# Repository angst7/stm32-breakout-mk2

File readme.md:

#STM32F4 development board#

ARMKit2 Breakout and development board for the 64-pin LQFP STM32F405 microcontroller.

The STM32F405 is a 32-bit ARM Cortex M4 micro manufactured by ST Microelectronics.

This PCB breaks out all the GPIO pins in two 2x16 pin 0.1" headers.  Power is provided by a USB mini-B connector through a 3.3v LDO regulator.  The USB data pins are routed to the port A USB peripheral in order to enable use of ST's built-in bootloader.  A Boot-select button is provided to enable this. 

The design is intended to be as bare-bones as possible, while enabling access to most of the important chip features.  Other features of this design are:

* Reset button.
* Two LEDs on-board.
* Optional External HS Oscillator
* Optional External RTC Oscillator
* Standard 6-Pin programming header for ST/Link
* 3mm mounting holes

Available as a shared project on [OSHPark](https://oshpark.com/profiles/MonkeyKungFu)

##Note regarding part population##

For STM32F405 parts, Populate C1 and C3 with 2.2uF capacitors.  Do not populate C5, R9.
For STM32F41x, STM32F4x1 parts, Populate R9 and C1 with 0 ohm Resistor.  Populate C5 with 4.7uF capacitor.  Do not populate C3.

##License##

This work is licensed under [CC Attribution 3.0 United States](https://creativecommons.org/licenses/by/3.0/us/).

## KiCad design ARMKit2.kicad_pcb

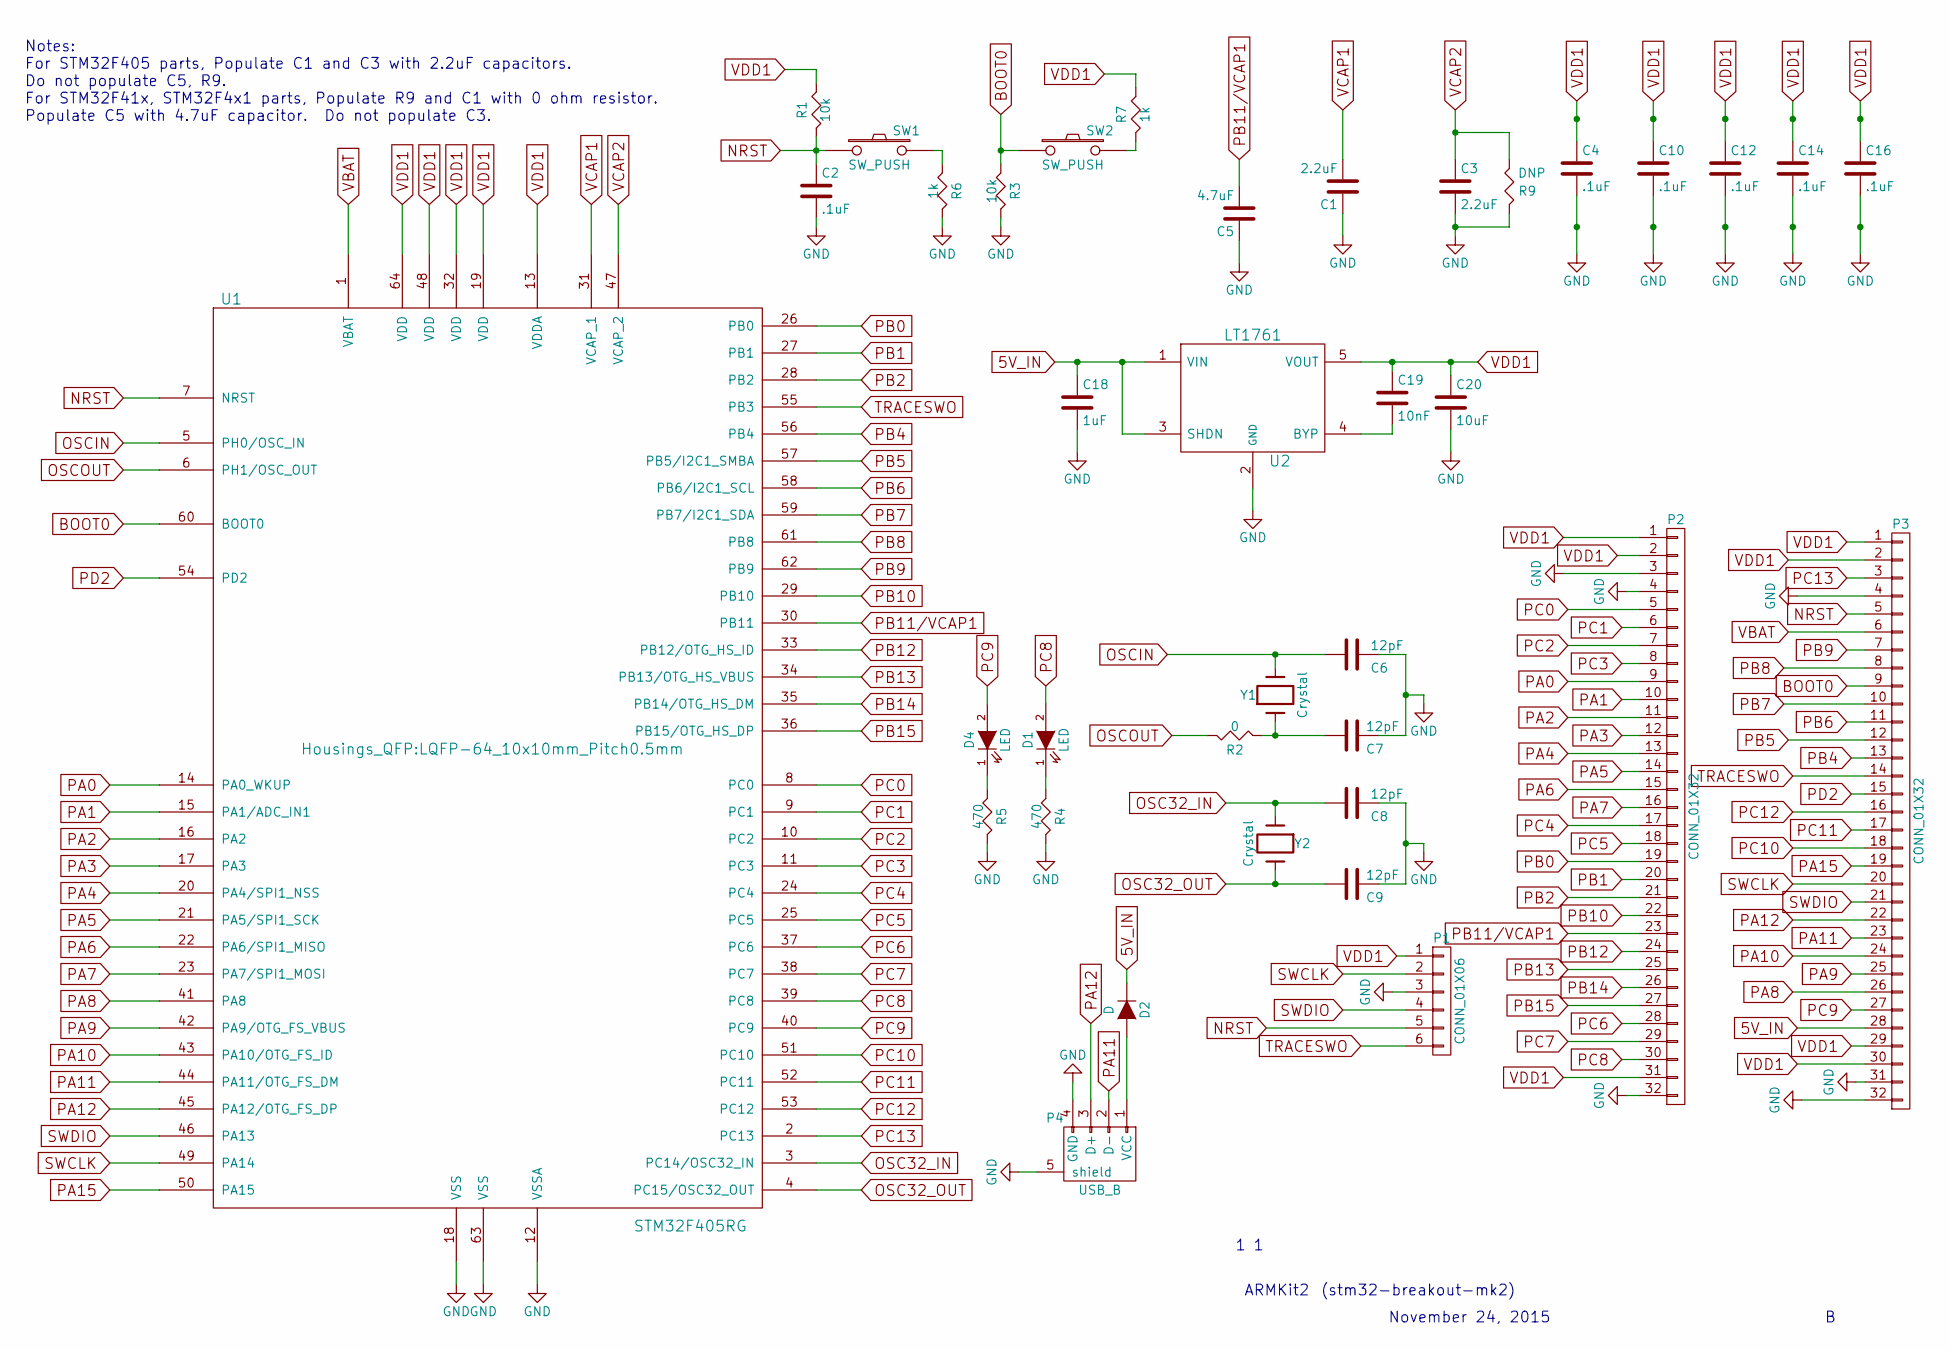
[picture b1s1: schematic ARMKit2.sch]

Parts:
C1, C3: 2.2uF; C_0805
C2, C4, C10, C12, C14, C16: .1uF; C_0805
C5: 4.7uF; C_0805
C6, C7, C8, C9: 12pF; C_0805
C18: 1uF; C_1210
C19: 10nF; C_0805
C20: 10uF; C_1210
D1, D4: LED; LED-0805
D2: D; SMD-1206_Pol
P1: CONN_01X06; Pin_Header_Straight_1x06
P2, P3: CONN_01X32; Pin_Header_Straight_2x16
P4: USB_B; USB_Mini-B
R1, R3: 10k; C_0805
R2: 0; C_0805
R4, R5: 470; C_0805
R6, R7: 1k; C_0805
R9: DNP; C_0805
SW1, SW2: SW_PUSH; SW_SPST_FSMSM
U1: STM32F405RG; LQFP-64_10x10mm_Pitch0.5mm
U2: LT1761; SOT-23-5
Y1: Crystal; Crystal_SMD_5032_2Pads
Y2: Crystal; SMD-1206_Pol

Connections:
5V_IN: C18.1, D2.1 (K), P3.28, U2.1 (VIN), U2.3 (SHDN)
BOOT0: P3.9, R3.1, SW2.1, U1.60 (BOOT0)
GND: C1.1, C2.2, C3.2, C4.2, C5.1, C6.1, C7.1, C8.1, C9.1, C10.2, C12.2, C14.2, C16.2, C18.2, C20.2, P1.3, P2.3, P2.4, P2.32, P3.4, P3.31, P3.32, P4.4 (GND), P4.5 (shield), R3.2, R4.2, R5.2, R6.2, R9.2, U1.12 (VSSA), U1.18 (VSS), U1.63 (VSS), U2.2 (GND)
NRST: C2.1, P1.5, P3.5, R1.1, SW1.1, U1.7 (NRST)
unnamed: C7.2, R2.1, Y1.1
unnamed: C19.2, U2.4 (BYP)
unnamed: D1.1 (K), R4.1
unnamed: D2.2 (A), P4.1 (VCC)
unnamed: D4.1 (K), R5.1
unnamed: R6.1, SW1.2
unnamed: R7.1, SW2.2
OSC32_IN: C8.2, U1.3 (PC14/OSC32_IN), Y2.1
OSC32_OUT: C9.2, U1.4 (PC15/OSC32_OUT), Y2.2
OSCIN: C6.2, U1.5 (PH0/OSC_IN), Y1.2
OSCOUT: R2.2, U1.6 (PH1/OSC_OUT)
PA0: P2.9, U1.14 (PA0_WKUP)
PA1: P2.10, U1.15 (PA1/ADC_IN1)
PA2: P2.11, U1.16 (PA2)
PA3: P2.12, U1.17 (PA3)
PA4: P2.13, U1.20 (PA4/SPI1_NSS)
PA5: P2.14, U1.21 (PA5/SPI1_SCK)
PA6: P2.15, U1.22 (PA6/SPI1_MISO)
PA7: P2.16, U1.23 (PA7/SPI1_MOSI)
PA8: P3.26, U1.41 (PA8)
PA9: P3.25, U1.42 (PA9/OTG_FS_VBUS)
PA10: P3.24, U1.43 (PA10/OTG_FS_ID)
PA11: P3.23, P4.2 (D-), U1.44 (PA11/OTG_FS_DM)
PA12: P3.22, P4.3 (D+), U1.45 (PA12/OTG_FS_DP)
PA15: P3.19, U1.50 (PA15)
PB0: P2.19, U1.26 (PB0)
PB1: P2.20, U1.27 (PB1)
PB2: P2.21, U1.28 (PB2)
PB4: P3.13, U1.56 (PB4)
PB5: P3.12, U1.57 (PB5/I2C1_SMBA)
PB6: P3.11, U1.58 (PB6/I2C1_SCL)
PB7: P3.10, U1.59 (PB7/I2C1_SDA)
PB8: P3.8, U1.61 (PB8)
PB9: P3.7, U1.62 (PB9)
PB10: P2.22, U1.29 (PB10)
PB11_VCAP1: C5.2, P2.23, U1.30 (PB11)
PB12: P2.24, U1.33 (PB12/OTG_HS_ID)
PB13: P2.25, U1.34 (PB13/OTG_HS_VBUS)
PB14: P2.26, U1.35 (PB14/OTG_HS_DM)
PB15: P2.27, U1.36 (PB15/OTG_HS_DP)
PC0: P2.5, U1.8 (PC0)
PC1: P2.6, U1.9 (PC1)
PC2: P2.7, U1.10 (PC2)
PC3: P2.8, U1.11 (PC3)
PC4: P2.17, U1.24 (PC4)
PC5: P2.18, U1.25 (PC5)
PC6: P2.28, U1.37 (PC6)
PC7: P2.29, U1.38 (PC7)
PC8: D1.2 (A), P2.30, U1.39 (PC8)
PC9: D4.2 (A), P3.27, U1.40 (PC9)
PC10: P3.18, U1.51 (PC10)
PC11: P3.17, U1.52 (PC11)
PC12: P3.16, U1.53 (PC12)
PC13: P3.3, U1.2 (PC13)
PD2: P3.15, U1.54 (PD2)
SWCLK: P1.2, P3.20, U1.49 (PA14)
SWDIO: P1.4, P3.21, U1.46 (PA13)
TRACESWO: P1.6, P3.14, U1.55 (PB3)
VBAT: P3.6, U1.1 (VBAT)
VCAP1: C1.2, U1.31 (VCAP_1)
VCAP2: C3.1, R9.1, U1.47 (VCAP_2)
VDD1: C4.1, C10.1, C12.1, C14.1, C16.1, C19.1, C20.1, P1.1, P2.1, P2.2, P2.31, P3.1, P3.2, P3.29, P3.30, R1.2, R7.2, U1.13 (VDDA), U1.19 (VDD), U1.32 (VDD), U1.48 (VDD), U1.64 (VDD), U2.5 (VOUT)

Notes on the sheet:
ARMKit2
November 24, 2015
(stm32-breakout-mk2)
Notes: For STM32F405 parts, Populate C1 and C3 with 2.2uF capacitors. Do not populate C5, R9. For STM32F41x, STM32F4x1 parts, Populate R9 and C1 with 0 ohm resistor. Populate C5 with 4.7uF capacitor. Do not populate C3.

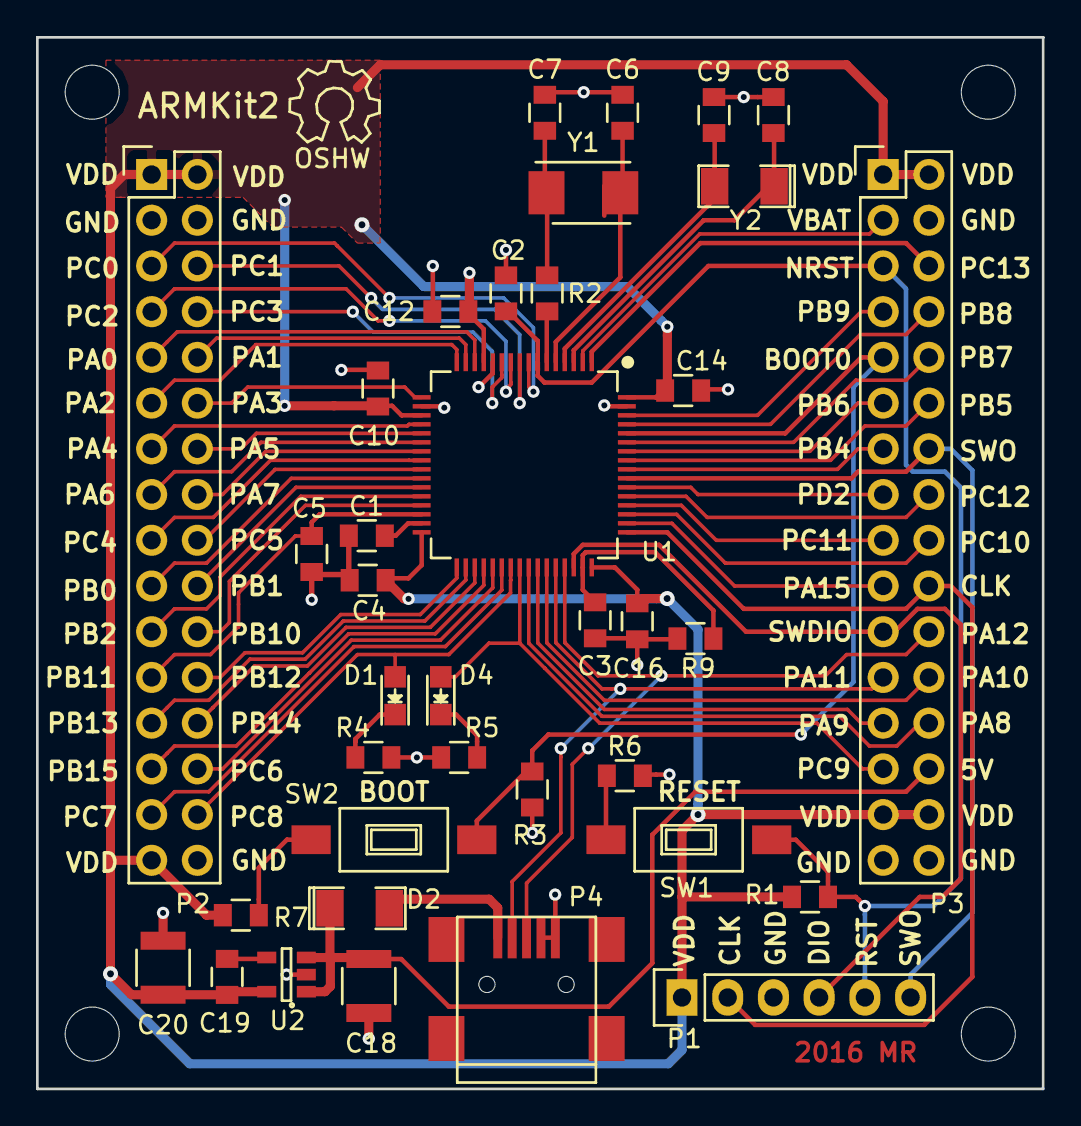
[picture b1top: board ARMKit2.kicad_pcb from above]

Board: 2 copper layers, 55.9 x 58.4 mm, 37 parts (0 on the bottom side), 66 nets.

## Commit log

2015-10-23 Added a bunch of traces
2015-10-23 More layout work.
2015-10-24 Finalized PCB
2015-11-11 Added some detail on the silk layer
2015-11-16 Added VBAT to breakout header, cleaned up RES fp size, cleaned up silkscreen
2015-11-16 Fixed broken track
2015-11-16 Removed some untracked files, updated gitignore
2015-11-17 Moved USB to PA11/PA12
2015-11-17 Added BOOT and RESET buttons, much re-routing
2015-11-24 Cleaned up some unused caps, added CC Attribution license
2015-11-24 Updated Gerbers to new name format
2015-11-25 More small changes to PCB, Schematic. Gerber refresh
2015-11-25 Moved traces that were too close to through-hole headers. Thanks @_madworm_
2015-12-07 Updated some 3d model settings
2015-12-19 Fixed BOOT0 pullup resistor value
2016-03-18 Added BOM
2016-05-11 Added LTC6247 symbol
2016-06-24 Added STM32F411, LTC6234
2016-06-25 Updated for STM32F41x, STM32F4x1 compatibility
2016-06-25 Added population notes
2016-06-26 Moved outline, can direct upload to OSHPark
2020-05-16 R7 1k
